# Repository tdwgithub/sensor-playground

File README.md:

# sensor-playground

Indoor Air-Quality Monitor / Sensor Playground Project

Copyright Notice

Copyright (c) 2022, tdwgithub
All rights reserved.

Redistribution and use in source and binary forms, with or without
modification, are permitted provided that the following conditions are met:
1. Redistributions of source code must retain the above copyright notice, this
   list of conditions and the following disclaimer.
2. Redistributions in binary form must reproduce the above copyright notice,
   this list of conditions and the following disclaimer in the documentation
   and/or other materials provided with the distribution.
THIS SOFTWARE IS PROVIDED BY THE COPYRIGHT HOLDERS AND CONTRIBUTORS "AS IS"
AND ANY EXPRESS OR IMPLIED WARRANTIES, INCLUDING, BUT NOT LIMITED TO, THE
IMPLIED WARRANTIES OF MERCHANTABILITY AND FITNESS FOR A PARTICULAR PURPOSE ARE
DISCLAIMED. IN NO EVENT SHALL THE COPYRIGHT HOLDER OR CONTRIBUTORS BE LIABLE
FOR ANY DIRECT, INDIRECT, INCIDENTAL, SPECIAL, EXEMPLARY, OR CONSEQUENTIAL
DAMAGES (INCLUDING, BUT NOT LIMITED TO, PROCUREMENT OF SUBSTITUTE GOODS OR
SERVICES; LOSS OF USE, DATA, OR PROFITS; OR BUSINESS INTERRUPTION) HOWEVER
CAUSED AND ON ANY THEORY OF LIABILITY, WHETHER IN CONTRACT, STRICT LIABILITY,
OR TORT (INCLUDING NEGLIGENCE OR OTHERWISE) ARISING IN ANY WAY OUT OF THE USE
OF THIS SOFTWARE, EVEN IF ADVISED OF THE POSSIBILITY OF SUCH DAMAGE.

INTRODUCTION

The Sensor Playground was designed to be a fun, easy-to-build platform for you
to experiment with software, sensors, displays, the IoT, etc.  It grew out of
a project I started after my wife suggested that some of the reasons for how
we had been feeling might be related to our indoor air-quality. 

It has been intentionally structured to make is straightforward for anyone 
with modest soldering skills and a bit of experience with tools like Arduino, 
to be able to construct a project that suits their ideas.

See: https://hackaday.io/project/182619-sensor-playground for more information.

It takes a kind-of "landing pad" approach, where you can build up the board 
and plug-in different kinds of processor modules, sensor sub-modules, displays,
etc. without the need to solder them directly to the board.  The number and 
variety of things you can plug in is virtually entirely up to you.

BUILDING YOUR OWN

There aren't a lot of "required" components, short of perhaps the power supply
section & the processor module and even that has been designed to give you a
wide range of choices.  

For example if you don't have a need for an encoder you don't need to install
it or its supporting pull-up resistors.  Same holds for the PCB-mount buttons.  As for
the sensors, I designed the PCB so that the processor I2C bus, SPI bus and a UART
are available via sockets or pins at a number of locations across the board.
This lets you connect the devices you choose at the points that make sense to
your particular application.  While there are outlines for some of the sensors
that I chose to use, these are by no means the ones you have to select.

3.3V, 5.0V & GND are made available on most connectors, so that it's easy to 
find a nearby power connection.

The component mounting types are all through-hole, making it pretty simple to
solder in what you want and there is a fair amount of space to get your soldering
iron into the places you need it to go.

SURFACE MOUNT COMPONENTS...! (relax, they're optional!)

I did add one (optional) surface-mount component: A processor reset controller.

If the processor module you choose doesn't already provide a power-on reset, or
perhaps its unreliable, then you can elect to install this component.  It's only
three pins and should be relatively easy for those with basic soldering skills and
a reasonably steady hand to install.  The only other component needed for the reset
circuit is a 100K, through-hole resistor.  See?  Not so hard after all!

PROCESSORS

I mentioned that you have flexibility in terms of your choice of processors.  This
is due to fact that the board has been designed to take one of two common processor
module types:

1. The ESP32 "DevKit"-style modules, from Esprssif, Inc.
2. A host of "Feather" form-factor modules.

The ESP32 modules are dual-core powerhouses, with WiFi, Bluetooth, large memory, etc.
If you have a processor-intensive application, the ESP32 is a great choice.

The "Feather" modules are a form-factor and pin-functionality specification created
by AdaFruit.  These modules are available with a wide range of processors, memory, 
IO, etc. and the pin-out is nearly identical across them all.  To date, I've used
ESP8266 Feather modules, ESP32 modules (same processor as the ESP32 DevKit, 
different form-factor), & ARM Cortex M0.  Given the circuit design I've chosen, 
all of these work on the Sensor Playground board.

I chose to focus on I2C, SPI and UART as the primary mechanism for connecting with the
sensors, displays, and other IO.  This allows for a wide range of devices to be 
connected, while limiting the amount of digital IO that would otherwise need to be
provided across the PCB.  There are a few  GPIO pins available on one of 
the headers (the same pins I use for the encoder and its button, along with the PCB-
mount push buttons).  

What if I want other IO than just SPI, I2C or UART?

Glad you asked!  If you elect to use a Feather form-factor processor module, you could
be in luck!  That specification also allows for the addition of "Feather Wing" expansion
modules to be plugged onto the top of Feather processor modules.  You can find a
pretty wide range of IO option boards that should satisfy a pretty wide range of requirements.

Alternatively, you could build something that uses SPI or I2C to drive an ADC or DAC.  That
would provide a nice means for gaining analog I/O and would allow the addition of 
non bus-based sensors.  I'm considering designing an add-on to do just that.

How do I build this thing?

I'll be adding some construction guides soon.  These will give you hints about how to go
about building the version of the Sensor Playground that best suits your application 
needs.

To find the construction guides, along with tips, etc., look in the "doc" folder at the
top level of this project.

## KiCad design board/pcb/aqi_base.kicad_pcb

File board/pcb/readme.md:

KiCad PCB layout file

Copyright Notice

Copyright (c) 2022, tdwgithub All rights reserved.

Redistribution and use in source and binary forms, with or without modification, are permitted provided that the following conditions are met:

Redistributions of source code must retain the above copyright notice, this list of conditions and the following disclaimer.
Redistributions in binary form must reproduce the above copyright notice, this list of conditions and the following disclaimer in the documentation and/or other materials provided with the distribution. THIS SOFTWARE IS PROVIDED BY THE COPYRIGHT HOLDERS AND CONTRIBUTORS "AS IS" AND ANY EXPRESS OR IMPLIED WARRANTIES, INCLUDING, BUT NOT LIMITED TO, THE IMPLIED WARRANTIES OF MERCHANTABILITY AND FITNESS FOR A PARTICULAR PURPOSE ARE DISCLAIMED. IN NO EVENT SHALL THE COPYRIGHT HOLDER OR CONTRIBUTORS BE LIABLE FOR ANY DIRECT, INDIRECT, INCIDENTAL, SPECIAL, EXEMPLARY, OR CONSEQUENTIAL DAMAGES (INCLUDING, BUT NOT LIMITED TO, PROCUREMENT OF SUBSTITUTE GOODS OR SERVICES; LOSS OF USE, DATA, OR PROFITS; OR BUSINESS INTERRUPTION) HOWEVER CAUSED AND ON ANY THEORY OF LIABILITY, WHETHER IN CONTRACT, STRICT LIABILITY, OR TORT (INCLUDING NEGLIGENCE OR OTHERWISE) ARISING IN ANY WAY OUT OF THE USE OF THIS SOFTWARE, EVEN IF ADVISED OF THE POSSIBILITY OF SUCH DAMAGE.

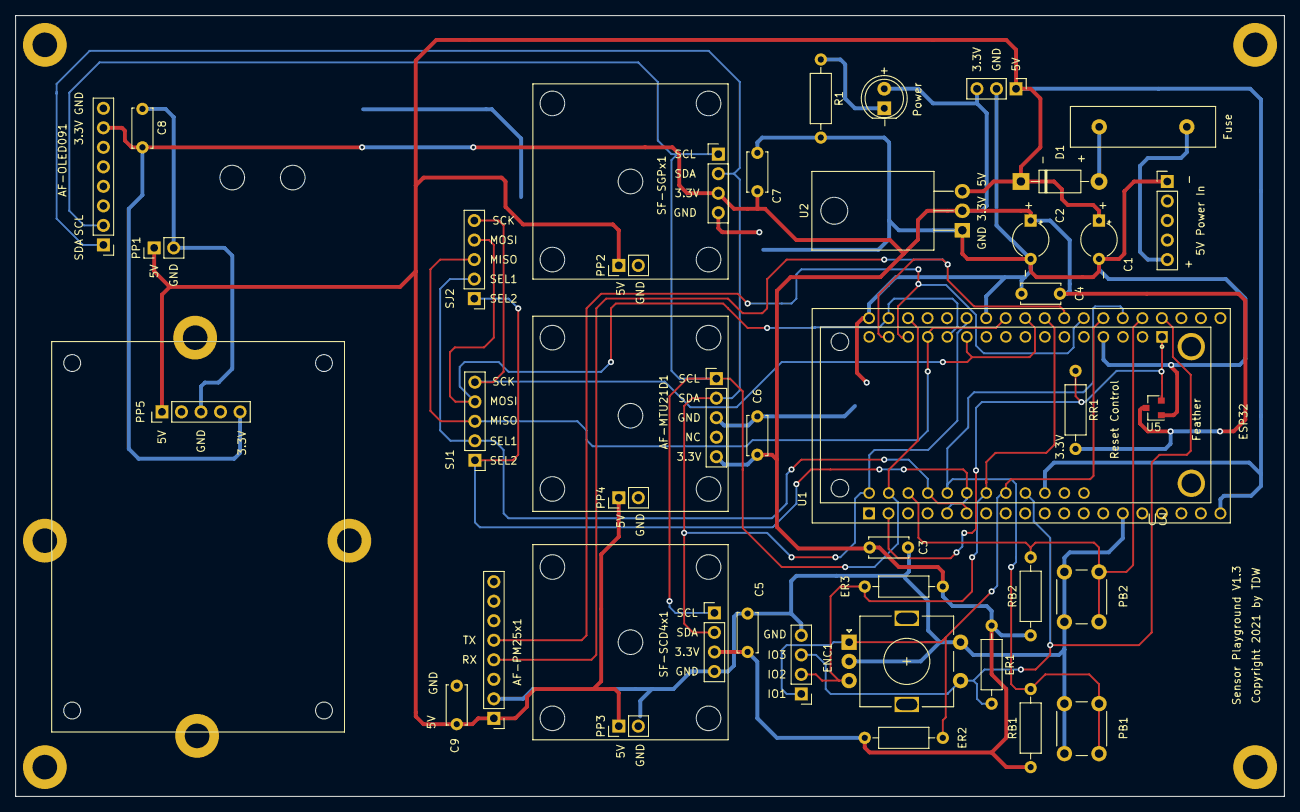
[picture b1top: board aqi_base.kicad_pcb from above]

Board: 2 copper layers, 165.1 x 101.6 mm, 41 parts (0 on the bottom side), 21 nets.

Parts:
AF-MTU21D1: Conn_01x05_Male; PinHeader_1x05_P2.54mm_Vertical
AF-OLED091: Conn_01x08_Male; PinHeader_1x08_P2.54mm_Vertical
AF-PM25x1: NC; PinHeader_1x08_P2.54mm_Vertical
C1, C2: 33uF; CP_Radial_Tantal_D4.5mm_P5.00mm
C3, C4, C5, C6, C7, C8, C9: .01uF; C_Disc_D5.0mm_W2.5mm_P5.00mm
D1: 1N4007; D_DO-41_SOD81_P10.16mm_Horizontal
ENC1: Rotary_Encoder_Switch; RotaryEncoder_Alps_EC11E-Switch_Vertical_H20mm
ER1, ER2, ER3: 10k; R_Axial_DIN0207_L6.3mm_D2.5mm_P10.16mm_Horizontal
F1: Fuse; Fuse_Littelfuse-LVR100
GPIO_HDR1: Conn_01x04_Male; PinHeader_1x04_P2.54mm_Vertical
LED1: LED; LED_D5.0mm
PB1, PB2: SW_Push_Dual_x2; SW_PUSH_6mm
PJ2: Conn_01x03_Male; PinHeader_1x03_P2.54mm_Vertical
PP1, PP2, PP3, PP4: Conn_01x02_Male; PinHeader_1x02_P2.54mm_Vertical
PP5: Conn_01x05_Male; PinHeader_1x05_P2.54mm_Vertical
R1: 10k; R_Axial_DIN0207_L6.3mm_D2.5mm_P10.16mm_Horizontal
RB1, RB2: 10k; R_Axial_DIN0207_L6.3mm_D2.5mm_P10.16mm_Horizontal
RR1: R_US; R_Axial_DIN0207_L6.3mm_D2.5mm_P10.16mm_Horizontal
SF-SCD4x1: Conn_01x04_Male; PinHeader_1x04_P2.54mm_Vertical
SF-SGPx1: Conn_01x04_Male; PinHeader_1x04_P2.54mm_Vertical
SJ1, SJ2: Conn_01x05_Male; PinHeader_1x05_P2.54mm_Vertical
U1: ESP32-DEVKITC-32D; MODULE_ESP32-DEVKITC-32D
U2: LM1117-3.3; TO-220-3_Horizontal_TabDown
U3: 2821; XCVR_2821
U5: MIC803-29D3VC3-TR; SOT-23
USB_Power1: Conn_01x05_Male; PinHeader_1x05_P2.54mm_Vertical

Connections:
3.3V: AF-MTU21D1.5, AF-OLED091.7, C2.1, C3.1, C4.1, C5.1, C6.1, C7.1, C8.1, ER1.1, ER2.1, ER3.2, LED1.2, PJ2.3, PP5.5, RB1.1, RB2.1, RR1.2, SF-SCD4x1.3, SF-SGPx1.3, U2.2, U5.3
5V: AF-PM25x1.1, C1.1, C9.1, D1.1, PJ2.1, PP1.1, PP2.1, PP3.1, PP4.1, PP5.1, U1.19, U2.3, U3.19
GND: AF-MTU21D1.3, AF-OLED091.8, AF-PM25x1.2, C1.2, C2.2, C3.2, C4.2, C5.2, C6.2, C7.2, C8.2, C9.2, ENC1.C, ENC1.S2, GPIO_HDR1.4, PB1.2, PB2.2, PJ2.2, PP1.2, PP2.2, PP3.2, PP4.2, PP5.3, R1.2, SF-SCD4x1.4, SF-SGPx1.4, U1.14, U1.20, U1.26, U2.1, U3.4, U5.1, USB_Power1.1
GPIO1: ENC1.A, ER2.2, GPIO_HDR1.1, U1.32, U3.21
GPIO2: ENC1.B, ER3.1, GPIO_HDR1.2, U1.29, U3.22
GPIO3: ENC1.S1, ER1.2, GPIO_HDR1.3, U1.35, U3.20
MISO: SJ1.3, SJ2.3, U1.27, U3.13
MOSI: SJ1.4, SJ2.4, U1.21, U3.12
unnamed: D1.2, F1.2
unnamed: F1.1, USB_Power1.5
unnamed: LED1.1, R1.1
PB1: PB1.1, RB1.2, U1.33, U3.24
PB2: PB2.1, RB2.2, U1.34, U3.26
RESET: RR1.1, U1.2, U3.1, U5.2
RXD: AF-PM25x1.5, U1.31, U3.14
SCK: SJ1.5, SJ2.5, U1.28, U3.11
SCL: AF-MTU21D1.1, AF-OLED091.2, SF-SCD4x1.1, SF-SGPx1.1, U1.22, U3.27
SDA: AF-MTU21D1.2, AF-OLED091.1, SF-SCD4x1.2, SF-SGPx1.2, U1.25, U3.28
SPI_SEL1: SJ1.2, SJ2.2, U1.6, U3.25
SPI_SEL2: SJ1.1, SJ2.1, U1.5, U3.23
TXD: AF-PM25x1.4, U1.30, U3.15

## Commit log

2022-03-02 Create src
2022-03-03 New version
2022-03-03 Initial BOM
2022-03-04 Added a CO2/CO level PDF
2022-03-04 Update to display missing reference designators
2022-03-06 Reorganized source code hierarchy.
2022-03-06 Adding the simple async timer class library.

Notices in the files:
board/pcb/aqi_base.kicad_pcb:
Copyright 2021 by TDW
